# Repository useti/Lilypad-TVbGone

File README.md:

# Lilypad arduino TV-B-Gone #

Small project of TV-B-Gone shield for lilypad arduino and arduino nano

# Nano shield #

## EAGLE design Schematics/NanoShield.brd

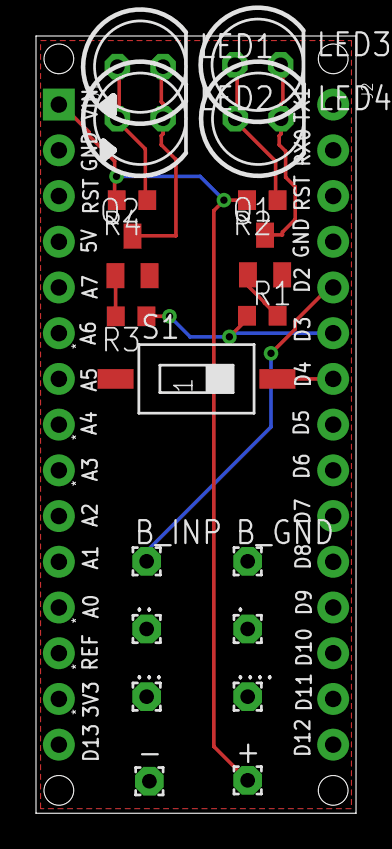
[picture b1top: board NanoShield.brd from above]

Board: 2 copper layers, 17.8 x 43.2 mm, 21 parts (0 on the bottom side), 11 nets.

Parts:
+: 1,6/0,8
-: 1,6/0,8
., .., ..., ....: 1,6/0,8
B_GND: 1,6/0,8
B_INP: 1,6/0,8
J1: HEAD15-NOSS
J2: HEAD15-NOSS-1
LED1, LED2, LED3, LED4: LED5MM
Q1, Q2: BCF81SMD; SOT23-BEC
R1, R2, R3, R4: R0603
S1: SWS001; SMS-001

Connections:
COM: -.1, ...1, J1.2, J2.4, Q1.E, Q2.E, S1.1
unnamed: J2.7, S1.2
unnamed: LED1.K, LED2.K, Q2.C
unnamed: LED3.K, LED4.K, Q1.C
unnamed: Q2.B, R3.2
unnamed: Q1.B, R1.2
unnamed: LED1.A, LED2.A, R4.1
unnamed: LED3.A, LED4.A, R2.1
unnamed: J2.6, R1.1, R3.1
unnamed: B_INP.1, J2.5
VIN: +.1, J1.1, R2.2, R4.2

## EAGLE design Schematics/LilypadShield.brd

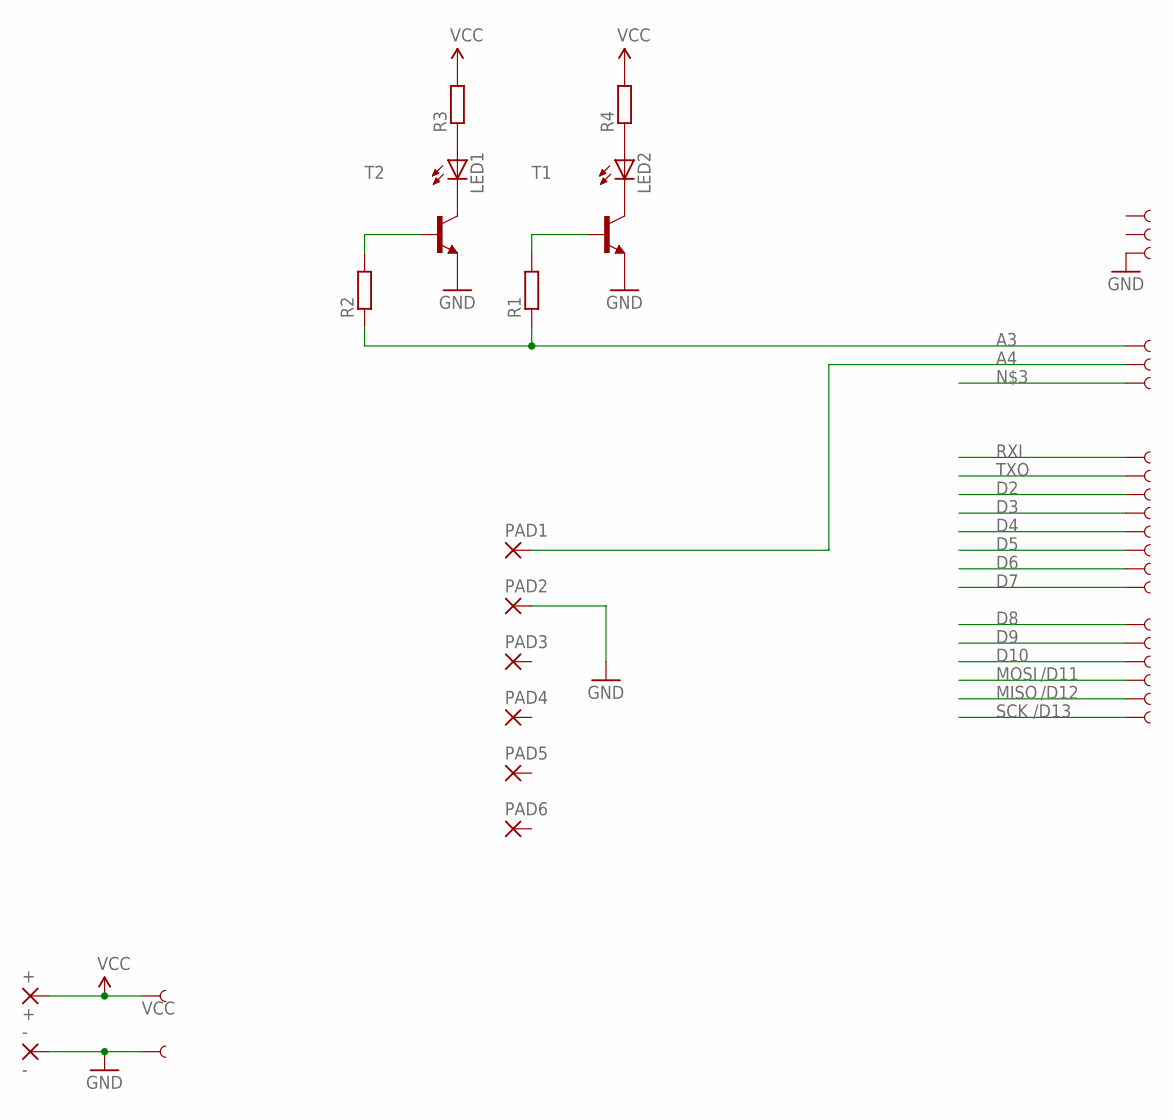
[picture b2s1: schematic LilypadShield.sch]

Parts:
+: +; 1,6/0,8
-: -; 1,6/0,8
GND: SEWTAP1; SEWTAP
LED1, LED2: LED5MM
PAD1, PAD2, PAD3, PAD4, PAD5, PAD6: 1,6/0,8
R1, R2, R3, R4: R-EU_0204/5; 0204/5
T1, T2: TO92
U$4, U$30, U$31, U$32, U$33, U$34, U$35, U$36, U$37, U$38, U$39, U$40, U$41, U$42, U$43, U$44, U$45, U$46, U$47, U$48, U$51: SEWTAP1; SEWTAP

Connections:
A3: R1.1, R2.1, U$32.1
A4: PAD1.1, U$33.1
D2: U$45.1
D3: U$44.1
D4: U$43.1
D5: U$42.1
D6: U$41.1
D7: U$48.1
D8: U$35.1
D9: U$36.1
D10: U$37.1
GND: -.1, PAD2.1, T1.3 (E), T2.3 (E), U$30.1, U$31.1
MISO: U$39.1
MOSI: U$38.1
unnamed: LED1.K (C), T2.1 (C)
unnamed: LED2.K (C), T1.1 (C)
unnamed: R2.2, T2.2 (B)
unnamed: R1.2, T1.2 (B)
unnamed: LED1.A, R3.1
unnamed: LED2.A, R4.1
RXI: U$47.1
SCK: U$40.1
TXO: U$46.1
VCC: +.1, R3.2, R4.2, U$4.1

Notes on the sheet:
/D11
/D12
/D13

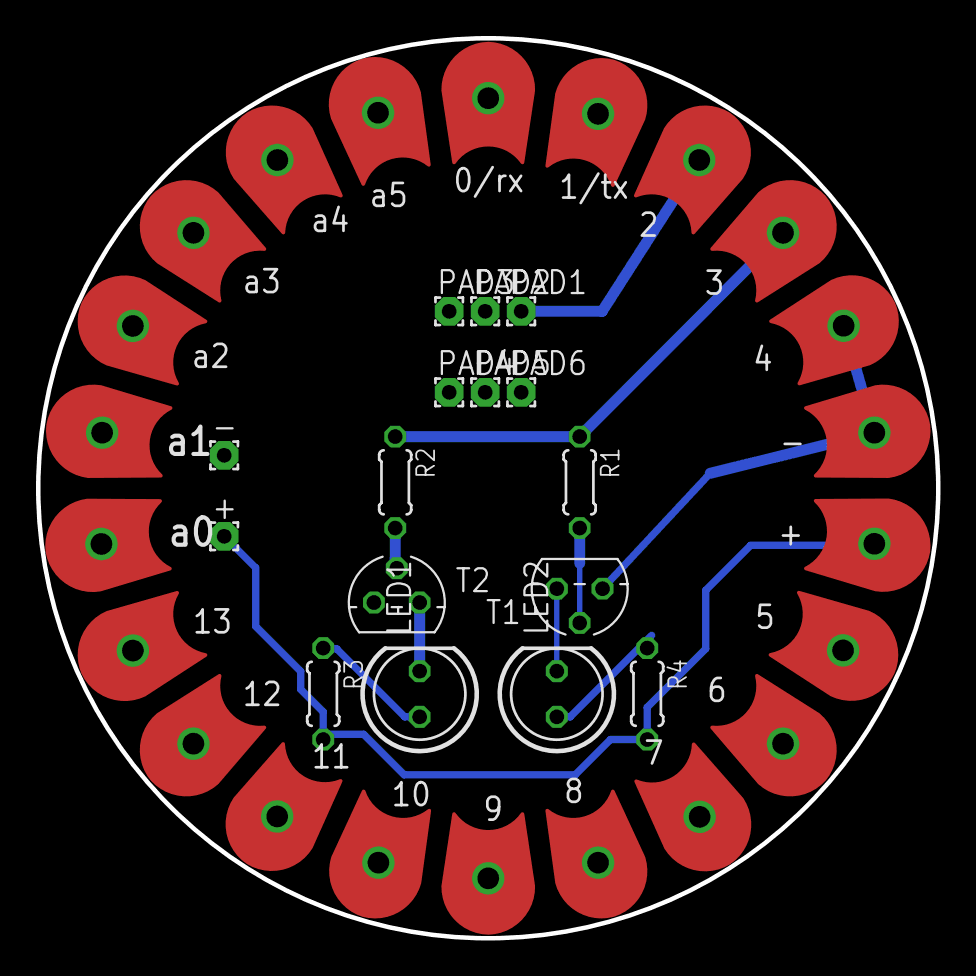
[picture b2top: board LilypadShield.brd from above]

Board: 2 copper layers, 50.0 x 50.0 mm, 38 parts (0 on the bottom side), 10 nets.

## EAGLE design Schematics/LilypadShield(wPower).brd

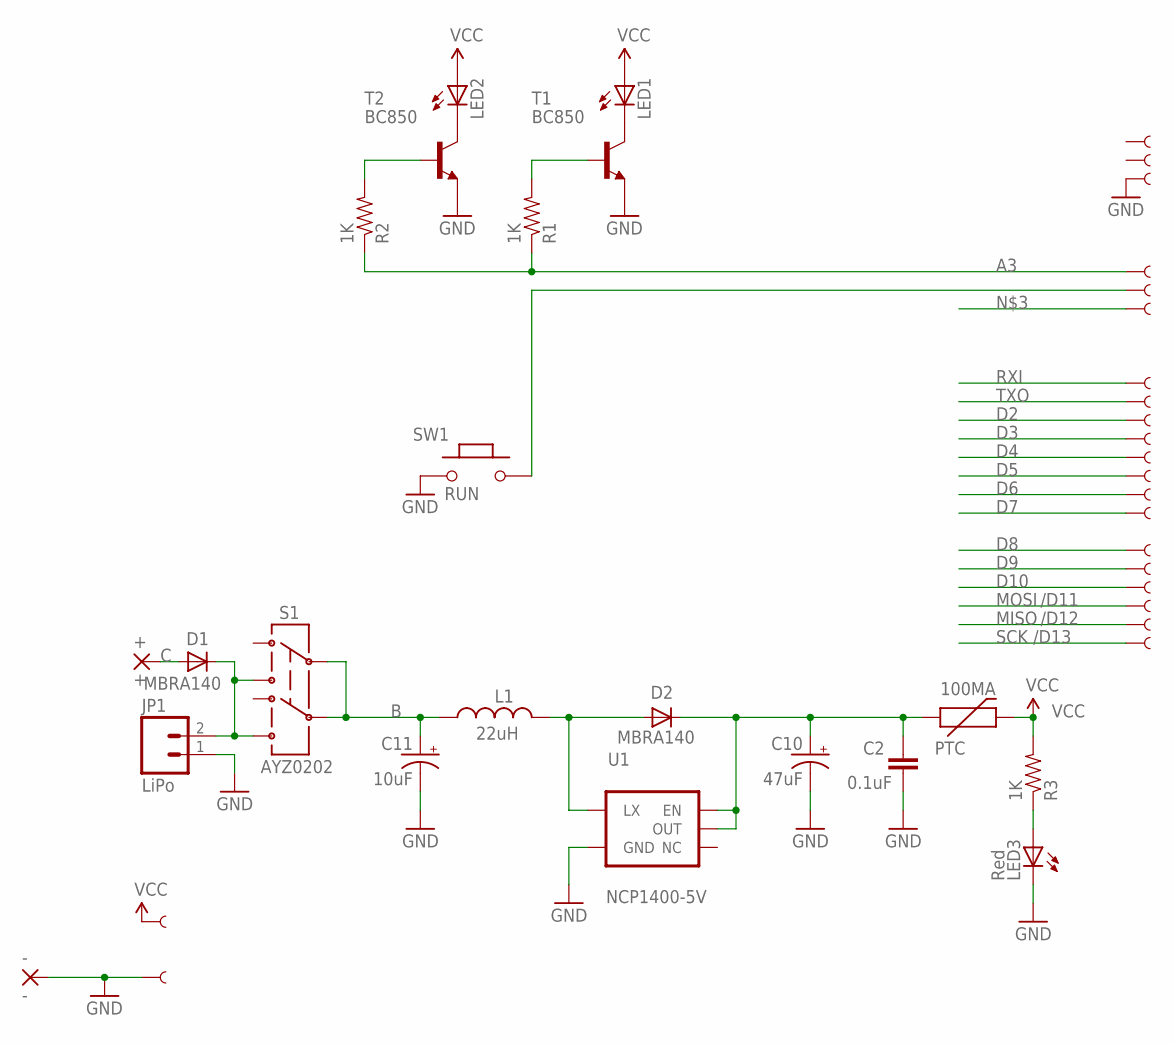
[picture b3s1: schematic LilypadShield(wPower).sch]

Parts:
100MA: PTC; PTC-1206
+: +; 1,6/0,8
-: -; 1,6/0,8
C2: 0.1uF; 0603-CAP
C10: 47uF; EIA3528-21
C11: 10uF; CPOL_1206
D1, D2: MBRA140; SMA-DIODE
GND: SEWTAP1; SEWTAP
JP1: LiPo; JST-2-SMD
L1: 22uH; CR54
LED1, LED2: LED5MM
LED3: Red; LED-1206
R1, R2, R3: 1K; 0603-RES
S1: AYZ0202
SW1: RUN; 157SW
T1, T2: BC850; SOT23
U1: NCP1400-5V; SOT23-5
U$4, U$30, U$31, U$32, U$33, U$34, U$35, U$36, U$37, U$38, U$39, U$40, U$41, U$42, U$43, U$44, U$45, U$46, U$47, U$48, U$51: SEWTAP1; SEWTAP

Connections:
A3: R1.1, R2.1, U$32.1
B: C11.A (+), L1.P$2 (2), S1.2, S1.5
C: +.1, D1.A
D2: U$45.1
D3: U$44.1
D4: U$43.1
D5: U$42.1
D6: U$41.1
D7: U$48.1
D8: U$35.1
D9: U$36.1
D10: U$37.1
GND: -.1, C2.2, C10.C (-), C11.C (-), JP1.1, LED3.C, SW1.1, T1.2 (E), T2.2 (E), U1.4 (GND), U$30.1, U$31.1
MISO: U$39.1
MOSI: U$38.1
unnamed: LED2.K (C), T2.3 (C)
unnamed: LED1.K (C), T1.3 (C)
unnamed: R2.2, T2.1 (B)
unnamed: R1.2, T1.1 (B)
unnamed: SW1.2, U$33.1
unnamed: LED3.A, R3.1
unnamed: 100MA.1, C2.1, C10.A (+), D2.C, U1.1 (EN), U1.2 (OUT)
unnamed: D1.C, JP1.2, S1.1 (3), S1.4 (6)
unnamed: D2.A, L1.P$1 (1), U1.5 (LX)
RXI: U$47.1
SCK: U$40.1
TXO: U$46.1
VCC: 100MA.2, LED1.A, LED2.A, R3.2, U$4.1

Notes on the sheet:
/D11
/D12
/D13

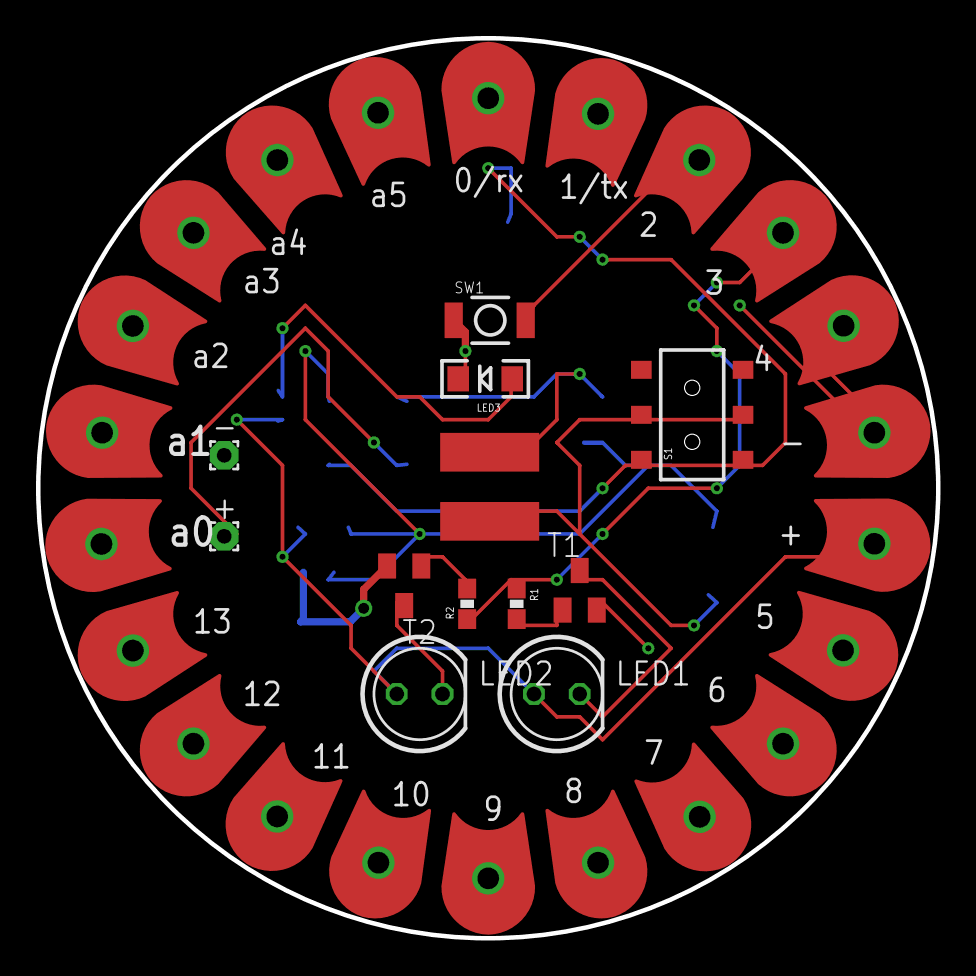
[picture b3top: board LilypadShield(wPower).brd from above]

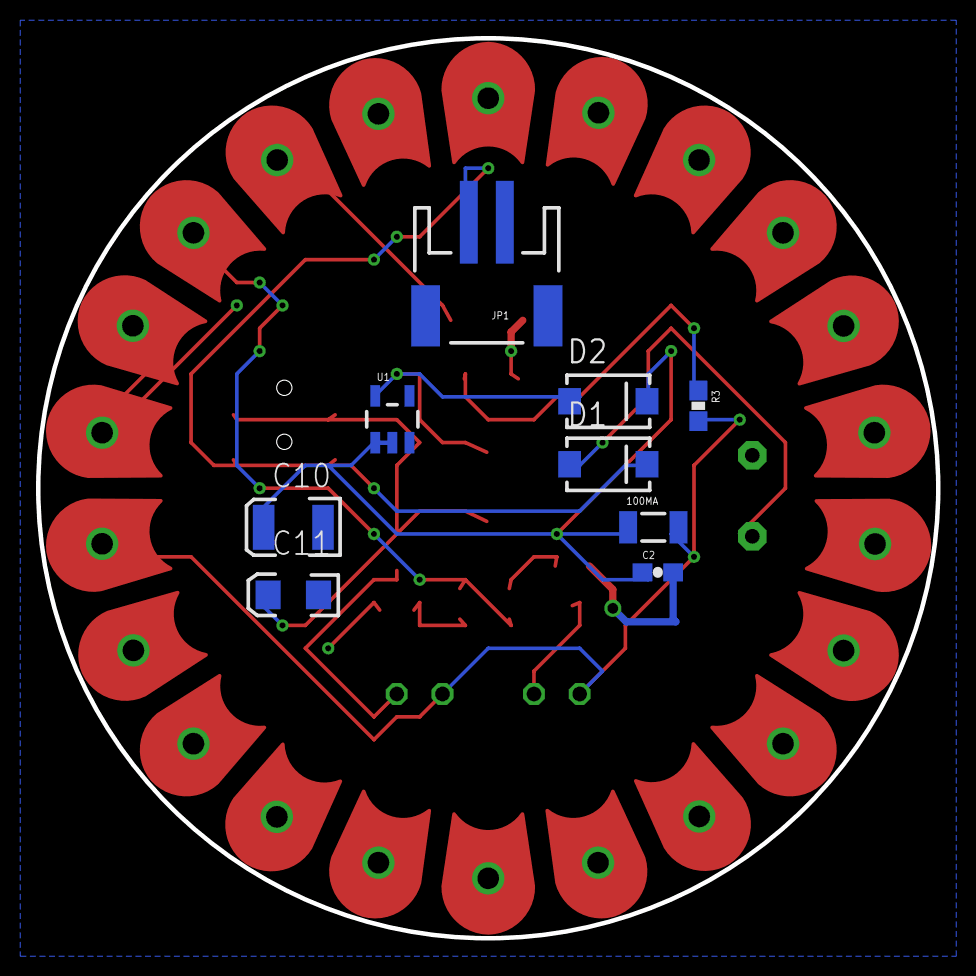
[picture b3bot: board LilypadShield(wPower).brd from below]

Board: 2 copper layers, 50.0 x 50.0 mm, 43 parts (9 on the bottom side), 14 nets.

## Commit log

2013-02-23 Initial commit new file: Mainboard-v18.brd new file: Mainboard-v18.sch
2013-02-23 modified: Mainboard-v18.brd new file: Mainboard-v18.pdf modified: Mainboard-v18.sch
2013-02-26 modified: Mainboard-v18.brd modified: Mainboard-v18.pdf modified: Mainboard-v18.sch new file: Mainboard-v18_top.pdf
2013-03-03 modified: Mainboard-v18.brd modified: Mainboard-v18.sch
2013-03-03 finish
2013-03-04 workaround
2013-05-01 Fixed for print
2013-05-01 initial
2013-05-01 Reorganize Folders
    Reorganized folders and added firmware. Fork of Ken Shirriff's
    Arduino-TV-B-Gone modified to run on Lilypad
2013-05-01 Readme
2013-05-01 Еще один маленький реорганайз директорий
2014-03-18 To print
2014-03-18 Design rules
2014-03-19 Images
2014-03-19 Images to readme
2014-03-21 New shields and rename
2014-03-22 Shield with smd elements and power supply
2014-03-24 Fixed board
2014-04-16 Ver.1
2014-04-20 More images
2014-09-15 Limiting resistors
2014-09-17 NanoShield
2014-09-17 Added nano shield image and changed readme.
2014-09-17 fixed one more time
2014-09-17 Yenka schematics modeL
2014-09-22 Model
2014-09-30 modified: Schematics/lamps.yka
2014-10-11 yenka
2014-10-11 Start new branch
2014-10-12 Redesign
